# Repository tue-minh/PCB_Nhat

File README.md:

# 📘 PCB Review 

---

## 🖼️ PCB Images

### 🔵 Front View

---

### 🔴 Back View

---

### 🟢 Routing View

---

## 📄 Schematic

📥 Nhấn vào link bên dưới để xem sơ đồ nguyên lý:

👉 [Open Schematic PDF](image/Schematic.pdf)

---

## 📝 Notes
- Kích thước mạch: 60 x 40 (mm)
- Khoảng cách lỗ: 54 x 34 (mm)
- Pinout: 

| ESP32  | HX711 | MPU6050 |
|--------|-------|---------|
| GPIO19 | DOUT1 |         |
| GPIO18 | SCK1  |         |
| GPIO16 | DOUT2 |         |
| GPIO17 | SCK2  |         |
| GPIO21 |       | SDA     |
| GPIO22 |       | SCL     |

---

## ✅ BOM
- [ ] SOC - ESP WROOM 32 (x1)
- [ ] IC - HX711 IC (x2)
- [ ] IC - CH340C (x1)
- [ ] IC - MPU6050 (x1)
- [ ] LDO - AMS1117 3V3 (x1)
- [ ] Transistor - SS8050 NPN (x2)
- [ ] Transistor - SS8550 PNP (x2)
- [ ] Button SMD - 3x6x2.5 (mm) (x2)
- [ ] Connector - TypeC 16P USB2.0 (x1)
- [ ] Connector - Terminal block 5.08 mm - 4 Pin (x2)
- [ ] Capacitor Tantalum - 3216 (Check schematic)
- [ ] Capacitor SMD - 0603 (Check schematic)
- [ ] Resistor SMD - 0603 (Check schematic)

---

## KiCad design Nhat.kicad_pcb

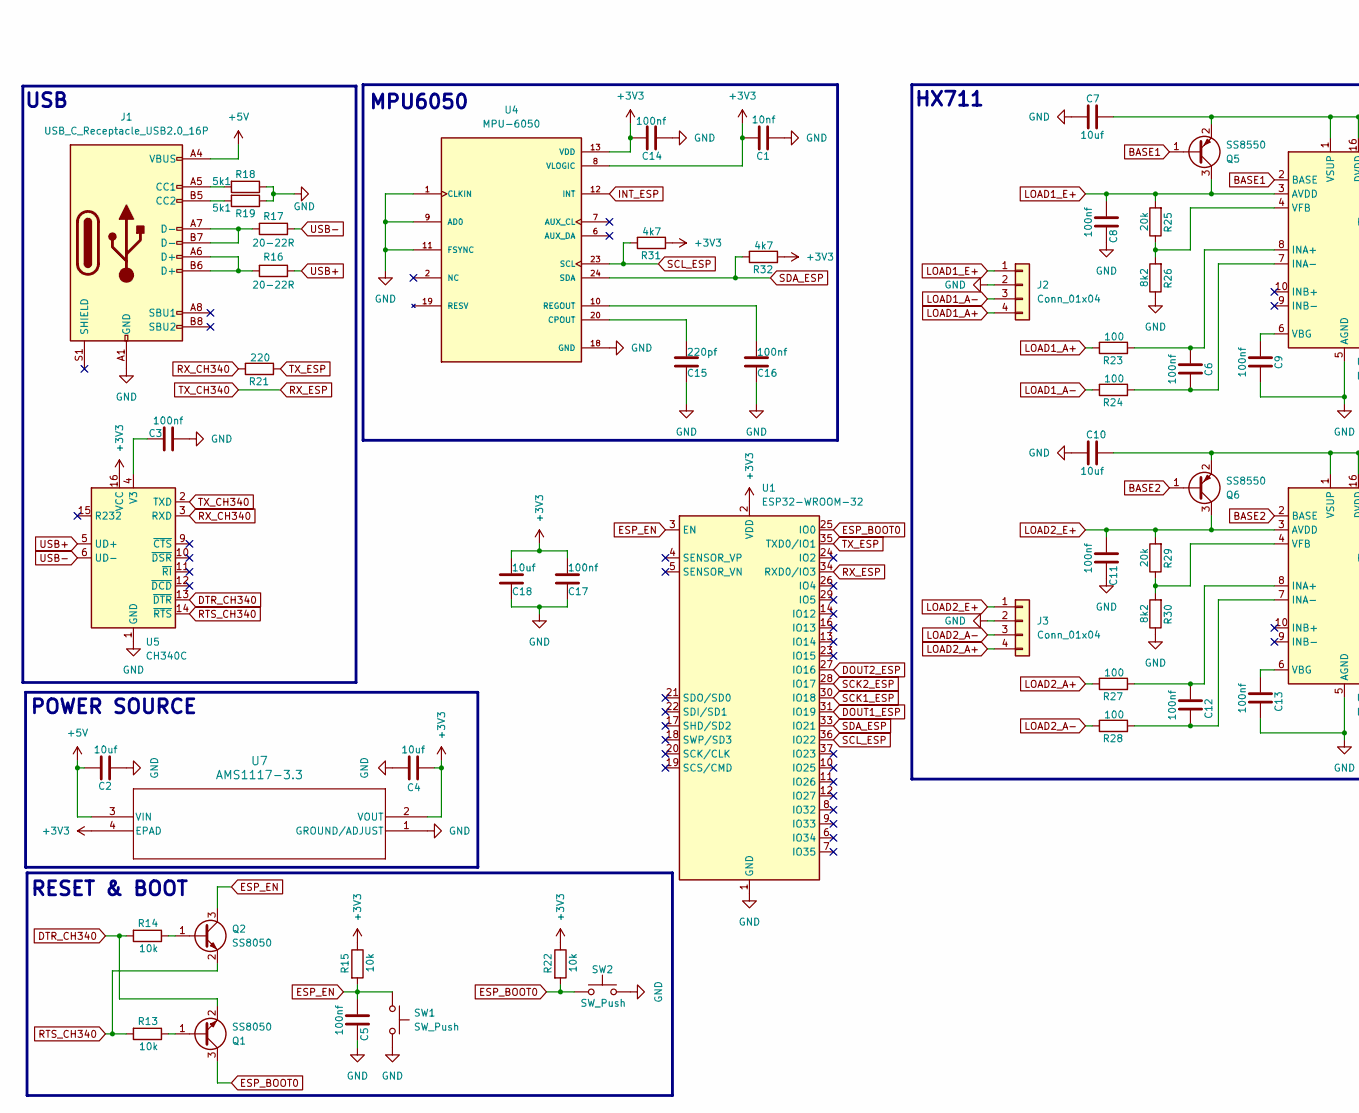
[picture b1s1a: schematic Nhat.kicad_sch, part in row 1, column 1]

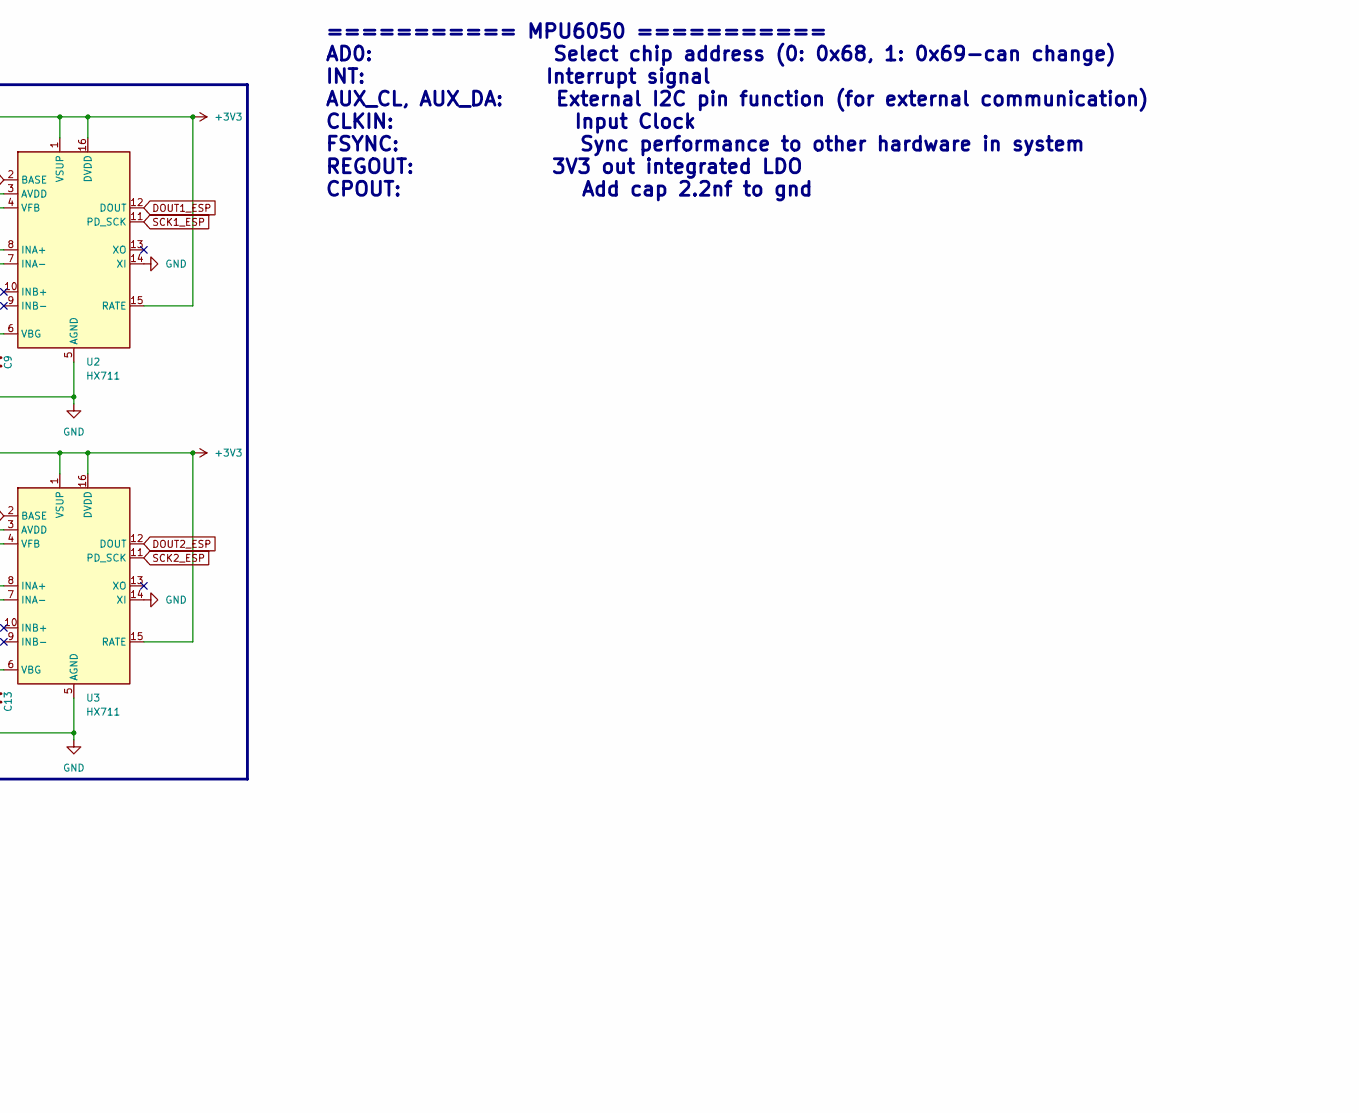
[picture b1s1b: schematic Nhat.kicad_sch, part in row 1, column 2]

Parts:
C1: 10nf; C_0603_1608Metric_Pad1.08x0.95mm_HandSolder
C2, C4: 10uf; CP_EIA-3216-12_Kemet-S_HandSolder
C3, C5, C6, C8, C9, C11, C12, C13, C14, C16, C17: 100nf; C_0603_1608Metric_Pad1.08x0.95mm_HandSolder
C7, C10, C18: 10uf; C_0603_1608Metric_Pad1.08x0.95mm_HandSolder
C15: 220pf; C_0603_1608Metric_Pad1.08x0.95mm_HandSolder
J1: USB_C_Receptacle_USB2.0_16P; USB_C_Receptacle_GCT_USB4105-xx-A_16P_TopMnt_Horizontal
J2, J3: Conn_01x04; TerminalBlock_Phoenix_MKDS-1,5-4-5.08_1x04_P5.08mm_Horizont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
Q1, Q2: SS8050; SOT-23
Q5, Q6: SS8550; SOT-23
R13, R14, R15, R22: 10k; R_0603_1608Metric_Pad0.98x0.95mm_HandSolder
R16, R17: 20-22R; R_0603_1608Metric_Pad0.98x0.95mm_HandSolder
R18, R19: 5k1; R_0603_1608Metric_Pad0.98x0.95mm_HandSolder
R21: 220; R_0603_1608Metric_Pad0.98x0.95mm_HandSolder
R23, R24, R27, R28: 100; R_0603_1608Metric_Pad0.98x0.95mm_HandSolder
R25, R29: 20k; R_0603_1608Metric_Pad0.98x0.95mm_HandSolder
R26, R30: 8k2; R_0603_1608Metric_Pad0.98x0.95mm_HandSolder
R31, R32: 4k7; R_0603_1608Metric_Pad0.98x0.95mm_HandSolder
SW1, SW2: SW_Push; tue_sw_smd_3x6x2.5mm
U1: ESP32-WROOM-32
U2, U3: HX711; SOP-16_3.9x9.9mm_P1.27mm
U4: MPU-6050; QFN50P400X400X95-24N; PARTREV 3.4
U5: CH340C; SOIC-16_3.9x9.9mm_P1.27mm
U7: AMS1117-3.3; SOT_AMS_ADS

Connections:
+3V3: C1.1, C4.1, C7.1, C10.1, C14.1, C17.1, C18.1, Q5.2 (E), Q6.2 (E), R15.1, R22.1, R31.2, R32.2, U1.2 (VDD), U2.1 (VSUP), U2.15 (RATE), U2.16 (DVDD), U3.1 (VSUP), U3.15 (RATE), U3.16 (DVDD), U4.8 (VLOGIC), U4.13 (VDD), U5.16 (VCC), U7.2 (VOUT), U7.4 (EPAD)
+5V: C2.1, J1.A4 (VBUS), J1.A9 (VBUS), J1.B4 (VBUS), J1.B9 (VBUS), U7.3 (VIN)
BASE1: Q5.1 (B), U2.2 (BASE)
BASE2: Q6.1 (B), U3.2 (BASE)
DOUT1_ESP: U1.31 (IO19), U2.12 (DOUT)
DOUT2_ESP: U1.27 (IO16), U3.12 (DOUT)
DTR_CH340: Q1.2 (E), R14.2, U5.13 (~DTR)
ESP_BOOT0: Q1.3 (C), R22.2, SW2.1, U1.25 (IO0)
ESP_EN: C5.2, Q2.3 (C), R15.2, SW1.1, U1.3 (EN)
GND: C1.2, C2.2, C3.2, C4.2, C5.1, C7.2, C8.1, C9.1, C10.2, C11.1, C13.1, C14.2, C15.2, C16.2, C17.2, C18.2, J1.A1 (GND), J1.A12 (GND), J1.B1 (GND), J1.B12 (GND), J2.2, J3.2, R18.1, R19.1, R26.1, R30.1, SW1.2, SW2.2, U1.1 (GND), U1.15 (GND), U1.38 (GND), U1.39 (GND), U2.5 (AGND), U2.14 (XI), U3.5 (AGND), U3.14 (XI), U4.1 (CLKIN), U4.9 (AD0), U4.11 (FSYNC), U4.18 (GND), U5.1 (GND), U7.1 (GROUND/ADJUST)
INT_ESP: U4.12 (INT)
LOAD1_A+: J2.4, R23.1
LOAD1_A-: J2.3, R24.1
LOAD1_E+: C8.2, J2.1, Q5.3 (C), R25.2, U2.3 (AVDD)
LOAD2_A+: J3.4, R27.1
LOAD2_A-: J3.3, R28.1
LOAD2_E+: C11.2, J3.1, Q6.3 (C), R29.2, U3.3 (AVDD)
unnamed: J1.A5 (CC1), R18.2
unnamed: J1.B5 (CC2), R19.2
unnamed: J1.A6 (D+), J1.B6 (D+), R16.1
unnamed: J1.A7 (D-), J1.B7 (D-), R17.1
unnamed: Q1.1 (B), R13.1
unnamed: Q2.1 (B), R14.1
unnamed: C6.2, R23.2, U2.8 (INA+)
unnamed: C6.1, R24.2, U2.7 (INA-)
unnamed: C9.2, U2.6 (VBG)
unnamed: R25.1, R26.2, U2.4 (VFB)
unnamed: C12.2, R27.2, U3.8 (INA+)
unnamed: C12.1, R28.2, U3.7 (INA-)
unnamed: C13.2, U3.6 (VBG)
unnamed: R29.1, R30.2, U3.4 (VFB)
unnamed: C15.1, U4.20 (CPOUT)
unnamed: C16.1, U4.10 (REGOUT)
unnamed: C3.1, U5.4 (V3)
RTS_CH340: Q2.2 (E), R13.2, U5.14 (~RTS)
RX_CH340: R21.1, U5.3 (RXD)
RX_ESP: U1.34 (RXD0/IO3), U5.2 (TXD)
SCK1_ESP: U1.30 (IO18), U2.11 (PD_SCK)
SCK2_ESP: U1.28 (IO17), U3.11 (PD_SCK)
SCL_ESP: R31.1, U1.36 (IO22), U4.23 (SCL)
SDA_ESP: R32.1, U1.33 (IO21), U4.24 (SDA)
TX_ESP: R21.2, U1.35 (TXD0/IO1)
USB+: R16.2, U5.5 (UD+)
USB-: R17.2, U5.6 (UD-)

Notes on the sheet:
USB
HX711
=========== MPU6050 =========== AD0: Select chip address (0: 0x68, 1: 0x69-can change) INT: Interrupt signal AUX_CL, AUX_DA: External I2C pin function (for external communication) CLKIN: Input Clock FSYNC: Sync performance to other hardware in system REGOUT: 3V3 out integrated LDO CPOUT: Add cap 2.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
RESET & BOOT
MPU6050
POWER SOURCE

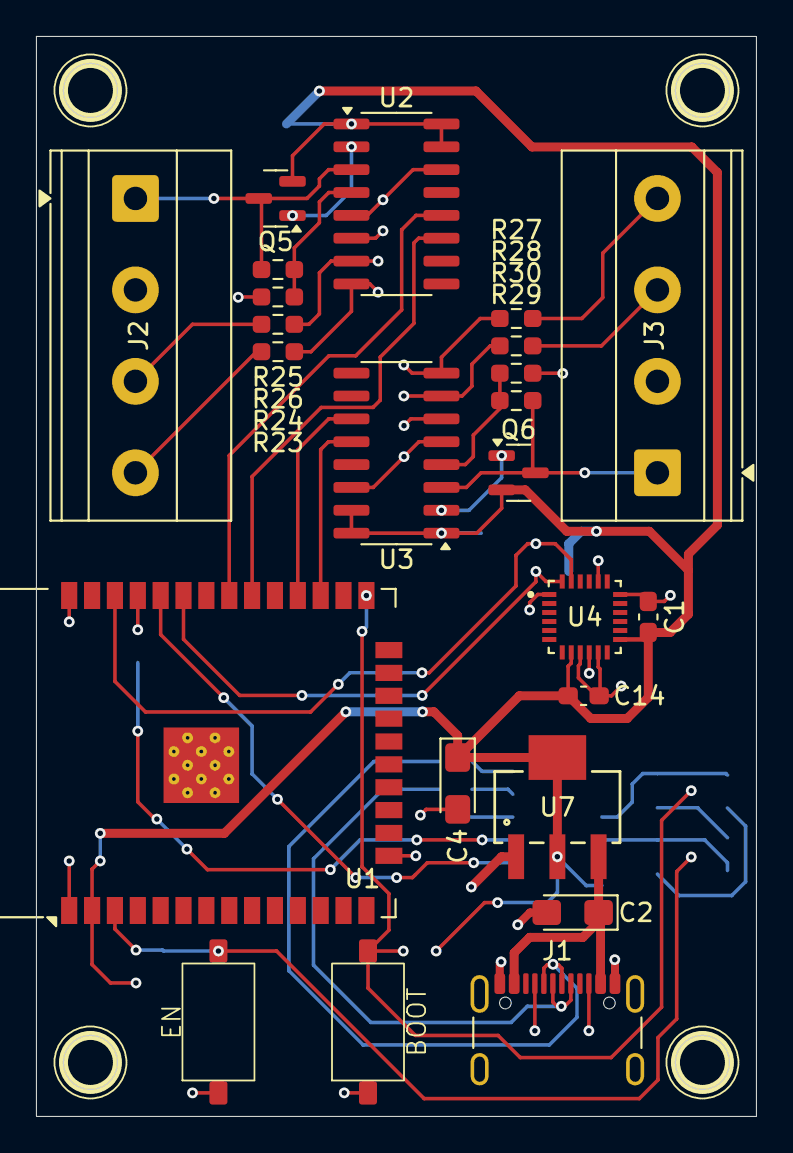
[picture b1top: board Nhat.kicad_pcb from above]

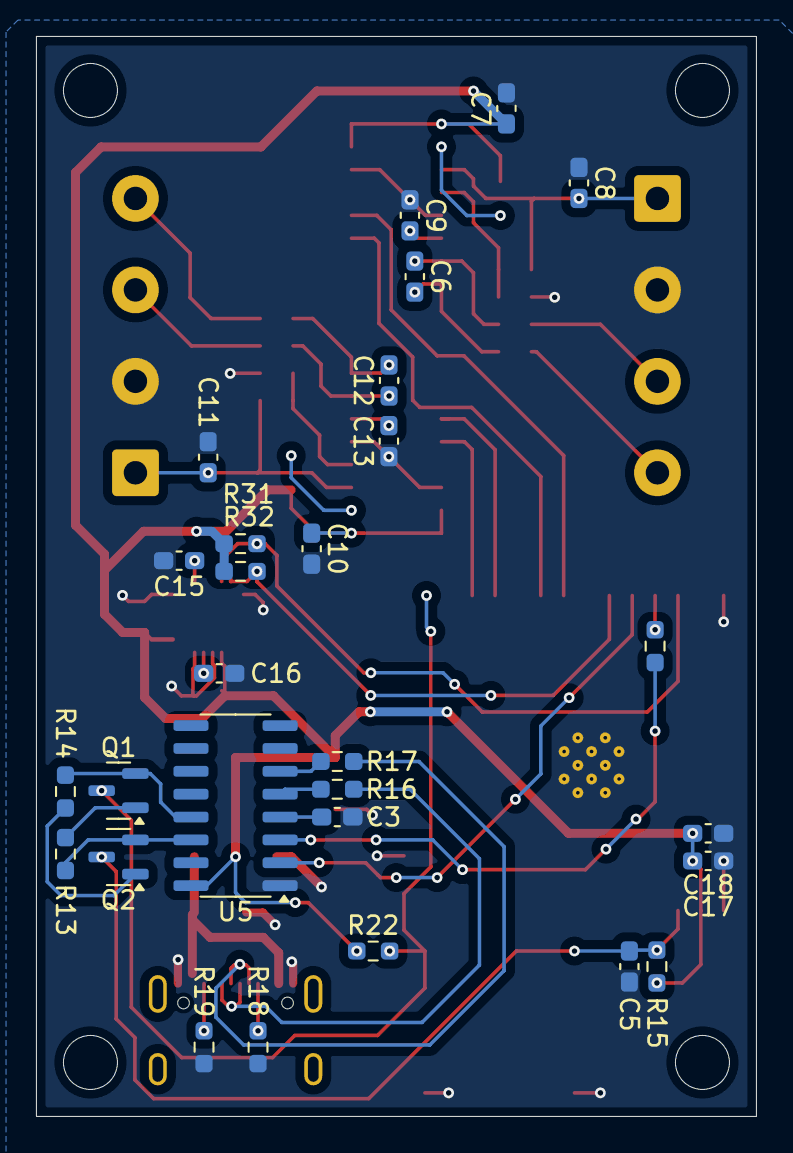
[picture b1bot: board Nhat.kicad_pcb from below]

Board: 2 copper layers, 40.0 x 60.0 mm, 52 parts (28 on the bottom side), 43 nets.

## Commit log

2026-03-31 update schematic, routing
2026-03-31 relocate workspace, update image
2026-03-31 update pinout
2026-04-01 add Led
2026-04-01 add gerber file
2026-04-09 update firmware
2026-04-09 update markdown file, relocate workspace
